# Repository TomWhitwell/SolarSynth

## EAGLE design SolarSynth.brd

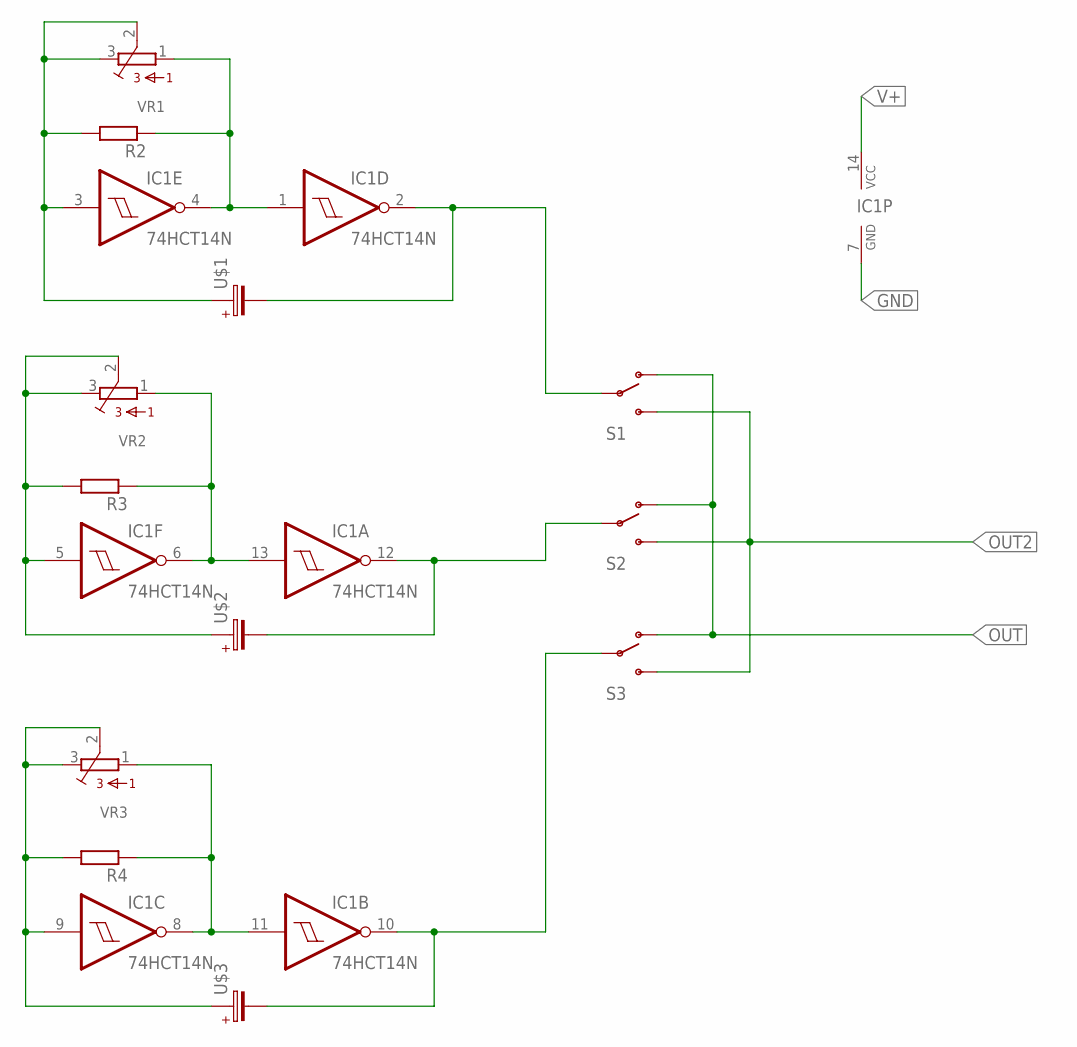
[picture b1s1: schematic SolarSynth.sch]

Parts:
IC1: 74HCT14N; DIL14
R2, R3, R4: R-EU_0207/7; 0207/7
S1, S2, S3: SWITCH-SPDTKIT; SWITCH-SPDT_KIT
U$1, U$2, U$3: 080-EU; 080_025
VR1, VR2, VR3: BOURNS_3362P_TRIMMERP; BOURNS_3362P_TRIMMER

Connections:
GND: IC1.7 (GND)
unnamed: IC1.1 (I), IC1.4 (O), R2.1, VR1.1
unnamed: IC1.3 (I), R2.2, U$1.+, VR1.2, VR1.3
unnamed: IC1.2 (O), S1.2, U$1.-
unnamed: IC1.5 (I), R3.2, U$2.+, VR2.2, VR2.3
unnamed: IC1.6 (O), IC1.13 (I), R3.1, VR2.1
unnamed: IC1.12 (O), S2.2, U$2.-
unnamed: IC1.9 (I), R4.2, U$3.+, VR3.2, VR3.3
unnamed: IC1.8 (O), IC1.11 (I), R4.1, VR3.1
unnamed: IC1.10 (O), S3.2, U$3.-
OUT: S1.1 (O), S2.1 (O), S3.1 (O)
OUT2: S1.3 (S), S2.3 (S), S3.3 (S)
V+: IC1.14 (VCC)

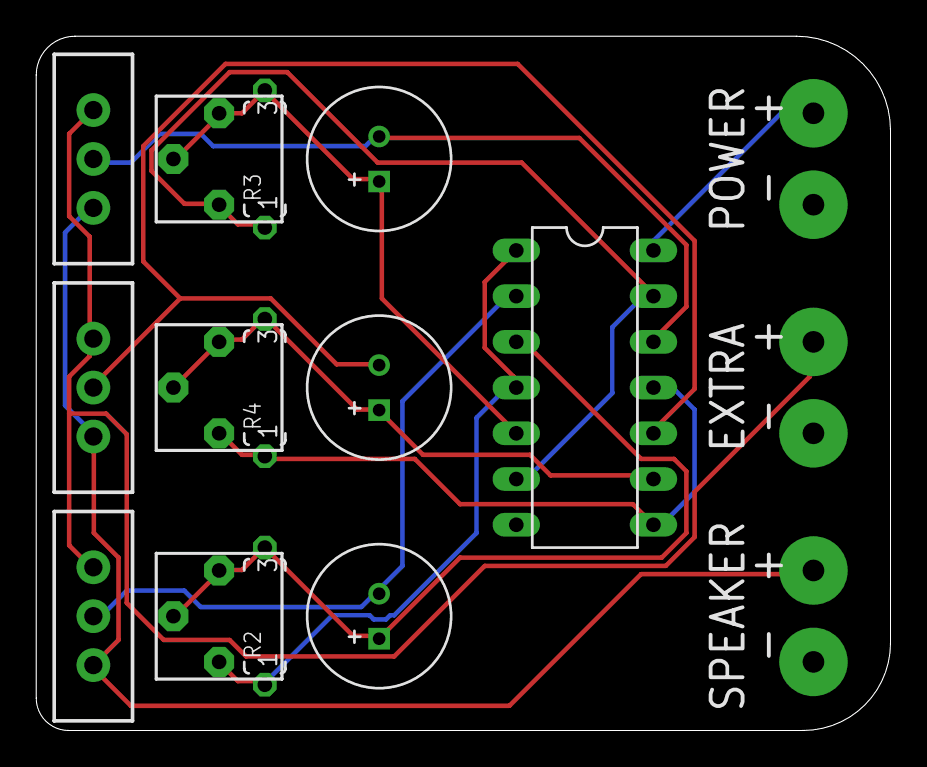
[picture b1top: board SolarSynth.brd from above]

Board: 2 copper layers, 47.5 x 38.6 mm, 14 parts (1 on the bottom side), 11 nets.

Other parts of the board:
U$4: MTM_1CM_KEEPOUT

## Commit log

2015-02-22 Early designs
2015-02-25 Cap changes
2015-03-24 Proto gerbers to OSH park
2015-03-24 test symlinks
2015-03-24 test using hard link
2015-03-24 link test
2015-03-24 remove test files

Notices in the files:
parts and their libraries:
SparkFun-Electromechanical: Licensing: CC v3.0 Share-Alike You are welcome to use this library for commercial purposes.
